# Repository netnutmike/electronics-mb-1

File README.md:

# electronics-mb
An open source electronics merit badge kit

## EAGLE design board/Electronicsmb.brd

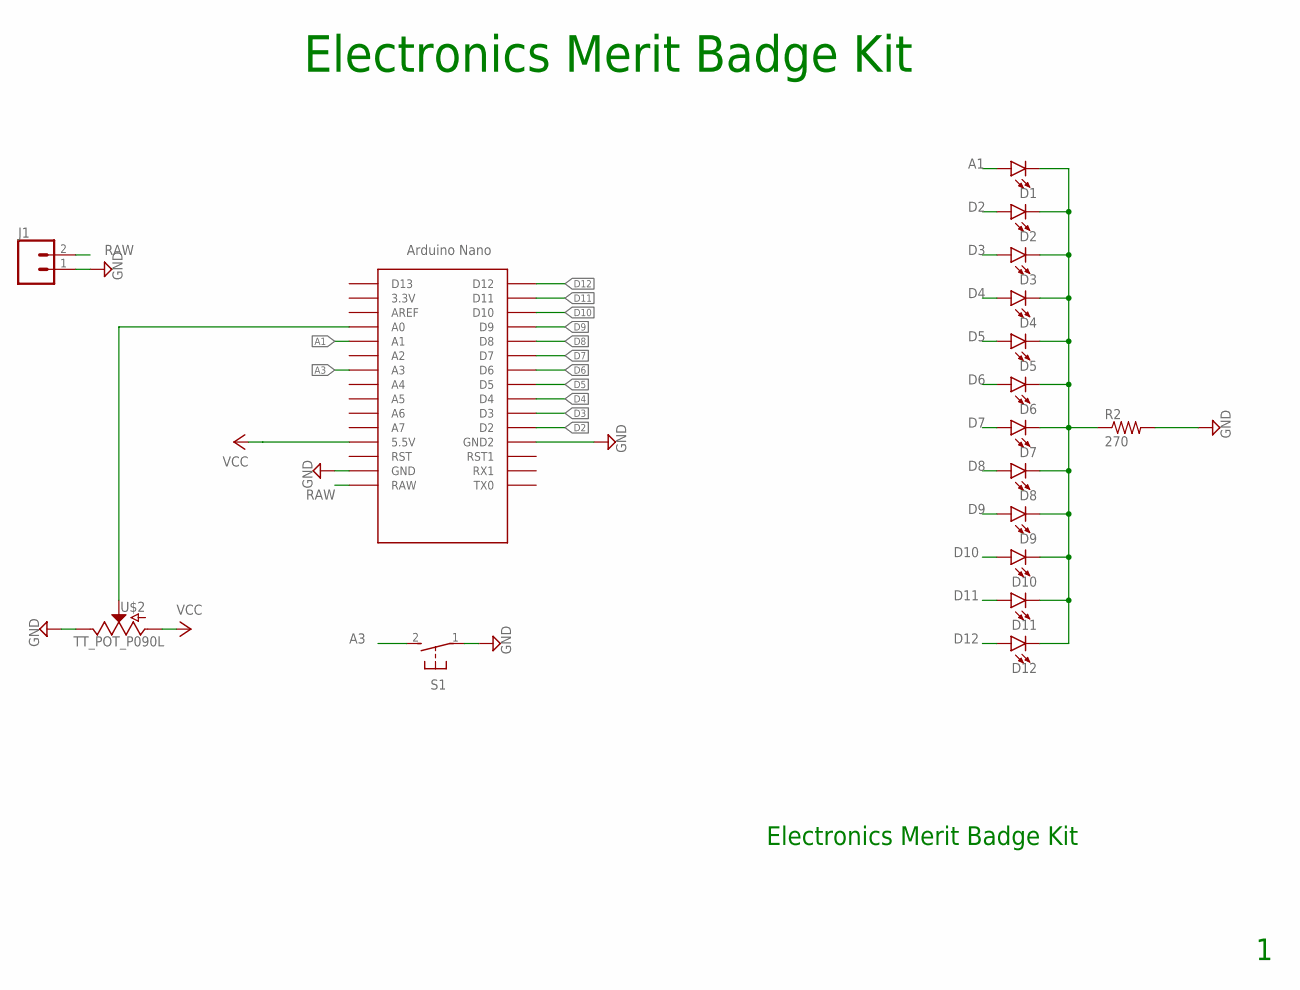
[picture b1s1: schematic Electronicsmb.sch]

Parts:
D1, D2, D3, D4, D5, D6, D7, D8, D9, D10, D11, D12: LED5MM; LED_5MM
J1: CONN_02; 1X02
R2: 270; AXIAL-0.4
S1: 31-XX; B3F-31XX
U$1: NANO
U$2: TT_POT_P090L; TT_POT

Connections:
A1: D1.A, U$1.A1
A3: S1.2 (S), U$1.A3
D2: D2.A, U$1.D2
D3: D3.A, U$1.D3
D4: D4.A, U$1.D4
D5: D5.A, U$1.D5
D6: D6.A, U$1.D6
D7: D7.A, U$1.D7
D8: D8.A, U$1.D8
D9: D9.A, U$1.D9
D10: D10.A, U$1.D10
D11: D11.A, U$1.D11
D12: D12.A, U$1.D12
GND: J1.1, R2.P$2 (2), S1.1, U$1.GND, U$1.GND1 (GND2), U$2.P$3 (E)
unnamed: D1.K (C), D2.K (C), D3.K (C), D4.K (C), D5.K (C), D6.K (C), D7.K (C), D8.K (C), D9.K (C), D10.K (C), D11.K (C), D12.K (C), R2.P$1 (1)
unnamed: U$1.A0, U$2.P$2 (S)
RAW: J1.2, U$1.RAW
VCC: U$1.5V (5.5V), U$2.P$1 (A)

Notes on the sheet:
Electronics Merit Badge Kit

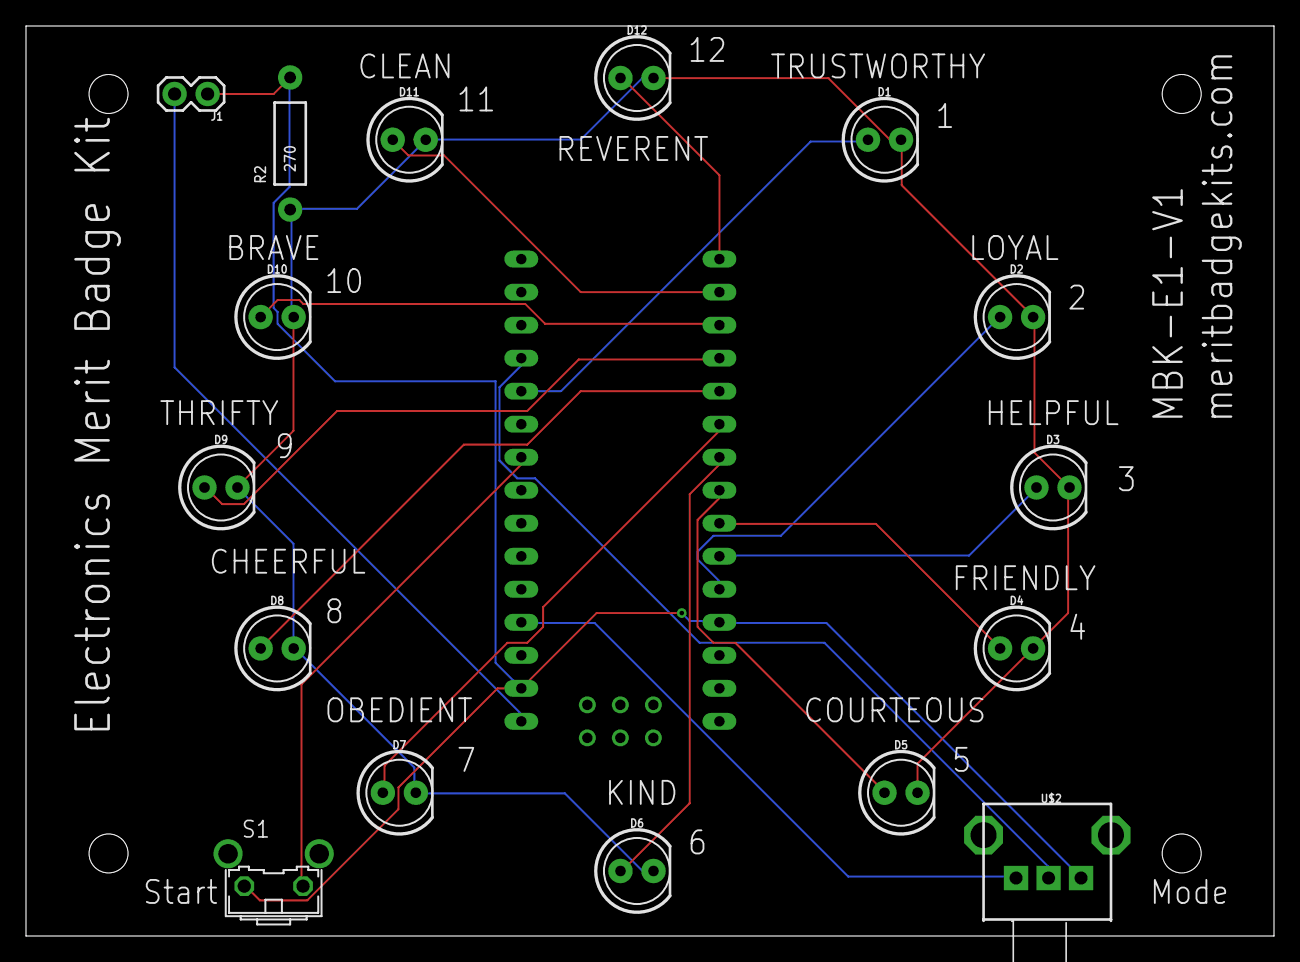
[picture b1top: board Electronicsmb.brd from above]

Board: 2 copper layers, 96.0 x 70.0 mm, 17 parts (0 on the bottom side), 18 nets.

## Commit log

2018-07-13 initial load
2018-07-13 CAM processor ran
2018-07-13 added drill holes
2018-07-13 Larger drill holes
2018-07-13 minor tweaks
2018-07-22 final tweaks to V1 and starter code
2018-09-28 Added pdf schematic
2018-10-12 adding latest version
2018-10-12 Latest Version
2018-10-12 cleanup

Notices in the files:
parts and their libraries:
SparkFun-LED: Licensing: Creative Commons ShareAlike 4.0 International - https://creativecommons.org/licenses/by-sa/4.0
SparkFun: Licensing: CC v3.0 Share-Alike You are welcome to use this library for commercial purposes.
